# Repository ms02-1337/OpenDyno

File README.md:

# OpenDyno - Open Dynamometer System

> Professional open-source motor dynamometer testing platform.

📖 **Read the full development story:** [Building a Dynamometer From Scratch](https://blog.ms02.es/posts/building-a-dynamometer-from-scratch/)

---

## Overview

**OpenDyno** is a complete open-source dynamometer software and hardware system designed for precise motor/engine performance testing. It is built primarily to control eddy current brakes (it should also support inertia brakes, though this is currently untested).

---

## Architecture

The project is divided into three core parts:

| Component     | Description |
|---------------|-------------|
| **DynoPower** | A power stage PCB designed to control the energy delivered to the eddy current brake. |
| **DynoLogic** | A control PCB running custom firmware. It is responsible for controlling the entire system, executing the logic software, running the PID loops, and managing all safety controls. |
| **DynoServer**| A Flask-based server that can run on a Raspberry Pi or any standard computer. It connects to DynoLogic via CAN bus and acts as the system's user interface. Using WebSockets, it serves a webpage to the browser, allowing the user to configure settings, start/stop tests, store and analyze data, and monitor the brake in real time. |

### Auxiliary Hardware
- **IGBT Power**: An auxiliary power supply board that converts AC mains to 15V to power the IGBT gate driver on the DynoPower board.
  - *Note*: This board is designed to output both +15V and -5V, but **only the positive (+15V) components need to be populated** for the OpenDyno system.

## System

### DynoLogic

### DynoPower

### DynoServer

---

## Key Features

- **Four Control Modes**: Constant Torque, Constant Speed, Dynamic Testing (automated state machine), and Acceleration Rate Control.
- **Real-Time Telemetry**: 100 Hz live data streaming (speed, torque, power, acceleration) via WebSocket.
- **PID Control**: High-frequency closed-loop PID control running at 1 kHz for maximum responsiveness.
- **Data Filtering**: Built-in signal processing including filters to ensure smooth and accurate sensor readings (e.g., from the load cell).
- **Thermal Monitoring**: Support for multiple temperature sensors to monitor brake and ambient temperatures.
- **Safety Limits**: User-configurable maximum speed and maximum PWM limits to protect the eddy current brake from thermal runaway, alongside minimum speed protection, a heartbeat watchdog, and emergency stop.
- **Web Interface**: Responsive UI with live charts.
- **Test Comparison**: Built-in capability to overlay and compare two different test runs directly within the user interface.
- **Selectable Power Units**: Toggle between Kilowatts (kW) and Horsepower (HP) for power measurements.

---

## Operating Modes

OpenDyno supports multiple test modes to thoroughly characterize your motor/engine:

### 1. Dynamic Mode
Automates an entire test run (e.g., accelerating from a minimum to a maximum speed and then decelerating). It uses a state machine to guarantee repeatable and standardized power sweeps.

### 2. Acceleration Mode
Maintains a constant acceleration rate (RPM/s) to smoothly sweep through the motor's power band, ensuring consistent and comparable power measurements regardless of the motor's natural acceleration.

### 3. Torque Mode
Applies a fixed braking torque to the motor regardless of the speed. Useful for thermal testing and checking steady-state efficiency under a specific load.

### 4. Speed Mode
Adjusts the braking force dynamically to hold the motor at an exact RPM, regardless of the throttle position. Perfect for mapping fuel or ignition tables across different RPM bands.

---

## Hardware Specifications

### DynoLogic Control Board
- **MCU**: Teensy 4.1 (600 MHz ARM Cortex-M7)
- **Encoder**: Quadrature input, 50 PPR ×4 (200 counts/rev) with DWT cycle-counter timing
- **Load Cell**: 24-bit ADC (HX711 or ADS1220 selectable at compile time)
- **Brake Control**: 16-bit PWM @ 1 kHz on pin 4
- **Sensors**: MLX90614 IR temperature, BME280 (T+RH), DS18B20, Hall current sensor
- **Communication**: CAN 2.0B @ 500 kbps + USB serial debug @ 500000 baud

### DynoPower Power Board
- **Power Stage**: IGBT-based eddy current brake power stage with isolated gate drive. Rated for up to 1200V and 160A.
- **Rectification**: GBJ5010 bridge rectifier + bulk capacitance
- **Protection**: Thermal monitoring
- **Connectors**: High-current power terminals + 4-pin control interface

### Pinouts & Connectors
See detailed pin assignments in `DynoLogic/README.md` and KiCad schematics.

---

## Getting Started

Building and configuring the OpenDyno system is a multi-step process that involves:

1. Manufacturing and assembling the PCBs (DynoPower, DynoLogic, IGBT Power).
2. Sourcing the components and sensors.
3. Wiring the system.
4. Flashing the DynoLogic firmware.
5. Deploying and configuring the DynoServer software.

To make this process as smooth as possible, we have compiled a comprehensive, chronological step-by-step guide.

> [!IMPORTANT]
> **Please follow the full setup guide here:** [GETTING_STARTED.md](GETTING_STARTED.md)

For detailed configuration parameters and deep-dive technical references, consult the respective component documentation:
- **DynoLogic Reference**: [DynoLogic/README.md](DynoLogic/README.md)
- **DynoPower Reference**: [DynoPower/README.md](DynoPower/README.md)
- **DynoServer Reference**: [DynoServer/README.md](DynoServer/README.md)

---

## Documentation

| Document | Location | Description |
|----------|----------|-------------|
| DynoLogic Reference | `DynoLogic/README.md` | Hardware assembly, firmware compilation, CAN protocol, and configuration parameters |
| DynoPower Reference | `DynoPower/README.md` | Complete guide for the IGBT power stage and brake driver |
| DynoServer Reference| `DynoServer/README.md` | Complete guide for headless Raspberry Pi deployment with systemd |

---

## Safety Warning

⚠️ **This system controls high-power rotating machinery and eddy current brakes.**

- Always use an emergency stop within immediate reach
- Verify all mechanical couplings before applying power
- Never exceed the mechanical or thermal limits of your brake or motor
- Test PID gains at low power first
- Follow all local electrical and mechanical safety regulations

---

## ⚠️ Critical Power-On Sequence

**DynoPower MUST be connected to AC mains ONLY AFTER DynoLogic has fully started and the web UI shows "Connected".**

Failure to follow this sequence can result in:
- Uncontrolled brake actuation on power-up
- Damage to power electronics or eddy current brake

**Correct startup order:**
1. Power on DynoLogic (Teensy boots, firmware initializes)
2. Start DynoServer and verify CAN connection (green "Connected" indicator)
3. **Then** apply AC mains power to DynoPower

**Shutdown order (reverse):**
1. Stop any running test via web UI
2. Remove AC mains power from DynoPower first
3. Power off DynoLogic / DynoServer

---

## Notes to Users

- The system has only been tested with a few amps of power, even though the IGBT supports up to 160A.
- The MAX22530AWE has not been tested in the system. The schematic measures voltage, but isolation has not been tested, and the code for it is not written yet.

---

## License

This project is released under the **Creative Commons Attribution-NonCommercial-ShareAlike 4.0 International (CC BY-NC-SA 4.0)** license:

- ✅ Free to use for personal, educational, and research purposes
- ✅ Must provide attribution to the original authors
- ❌ **Not permitted for commercial use** or any activity that generates revenue
- 🔄 Any modifications or derivative works **must be published** under the exact same license

See the full [LICENSE](LICENSE) file for legal text.

---

*Use at your own risk.*

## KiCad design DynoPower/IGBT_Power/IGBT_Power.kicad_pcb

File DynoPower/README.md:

# DynoPower

> Isolated power electronics board for eddy current brake control.

Part of the **OpenDyno** motor dynamometer system.

## Contents

- `DynoPower_v2/` – KiCad 7 project for the main brake driver
  - `lib/` – Custom component libraries and 3D STEP models
  - `bom/ibom.html` – Interactive bill of materials
- `IGBT_Power/` – KiCad 7 project for the IGBT Driver Power Supply

## Key Features

- IGBT-based brake driver with isolated gate drive (UCC5304)
- GBJ5010 bridge rectifier + bulk capacitance
- Snubber networks and protection circuitry
- High-current power terminals

## Important Safety & Operation Notes

> [!CAUTION]
> **HIGH VOLTAGE**: This board handles dangerous high voltages. Exercise extreme caution and do not touch the board or its terminals while it is powered on. Always allow time for the bulk capacitance to discharge after powering off before handling the board.

> [!WARNING]
> **POWER-ON SEQUENCE**: You must ALWAYS follow the correct power sequencing to avoid unexpected brake engagement or hardware damage:
> 1. Power on the **DynoLogic** controller first.
> 2. Ensure the DynoServer web interface shows a successful **Connected** status.
> 3. **ONLY THEN** should you connect the DynoPower board to AC mains.
> 4. When shutting down, disconnect DynoPower from AC mains *before* powering off DynoLogic.

> [!IMPORTANT]
> **THERMAL MANAGEMENT**: The IGBT on this board is rated for up to 160A. However, a typical eddy current brake will draw between 15A to 45A. If you are operating the brake under constant load for extended periods, the board **will require active cooling (fans)** and a substantial heatsink to dissipate the generated heat.

## Documentation

See the main [OpenDyno README](../README.md#hardware-specifications) for specifications and the KiCad project for schematics and fabrication files.

## License

Licensed under the OpenDyno custom non-commercial license. See root [LICENSE](../LICENSE).

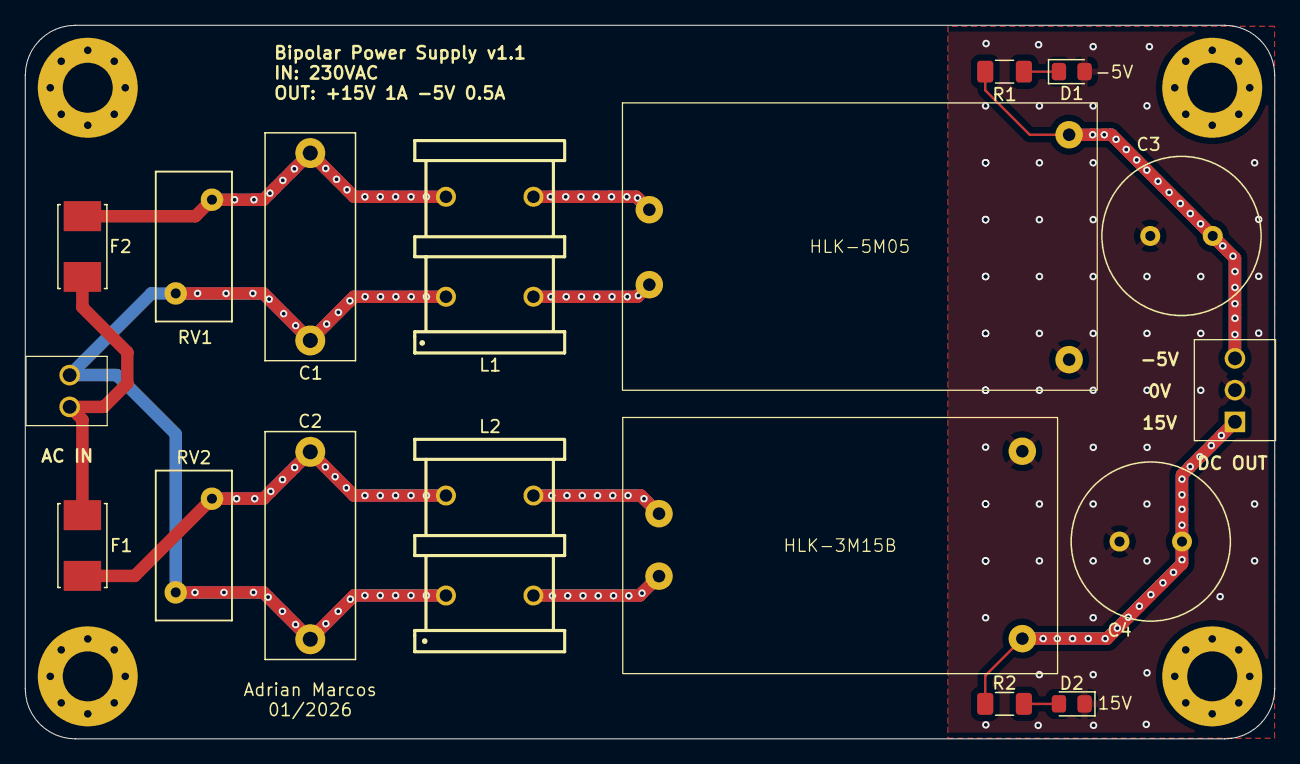
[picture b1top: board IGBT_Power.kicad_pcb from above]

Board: 2 copper layers, 100.0 x 57.1 mm, 22 parts (0 on the bottom side), 13 nets.

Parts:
C1, C2: 0.1uF; C_Rect_L18.0mm_W7.0mm_P15.00mm_FKS3_FKP3
C3, C4: 220uF; C_Radial_D12.5mm_H20.0mm_P5.00mm
D1: 5V; D_0805_2012Metric_Pad1.15x1.40mm_HandSolder
D2: 15V; D_0805_2012Metric_Pad1.15x1.40mm_HandSolder
F1: 1A; Fuseholder_Littelfuse_Nano2_157x
F2: 500mA; Fuseholder_Littelfuse_Nano2_157x
HLK-3M15B: HLK-3M15B
HLK-5M05: HLK-5M05
J1: IN; 2pin
J2: OUT; 3pin
L1, L2: 15mH; 15mH_Inductor
M2, M2#2, M2#3, M2#4: MountingHole_4mm_Pad_Via
R1: 220; R_1206_3216Metric_Pad1.30x1.75mm_HandSolder
R2: 1k; R_1206_3216Metric_Pad1.30x1.75mm_HandSolder
RV1, RV2: 10D561K; RV_Disc_D12mm_W6.1mm_P7.5mm

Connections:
+15V: C4.1, HLK-3M15B.4 (V+), J2.1, R2.1
-5V: C3.2, HLK-5M05.3 (V-), J2.3, R1.2
GND: C3.1, C4.2, D1.2 (A), D2.1 (K), HLK-3M15B.3 (V-), HLK-5M05.4 (V+), J2.2
unnamed: C1.1, F2.1, L1.1, RV1.1
unnamed: C2.1, F1.1, L2.1, RV2.1
unnamed: D1.1 (K), R1.1
unnamed: D2.2 (A), R2.2
unnamed: F1.2, F2.2, J1.1
unnamed: C1.2, C2.2, J1.2, L1.4, L2.4, RV1.2, RV2.2
unnamed: HLK-5M05.1 (AC), L1.2
unnamed: HLK-5M05.2 (AC), L1.3
unnamed: HLK-3M15B.1 (AC), L2.2
unnamed: HLK-3M15B.2 (AC), L2.3

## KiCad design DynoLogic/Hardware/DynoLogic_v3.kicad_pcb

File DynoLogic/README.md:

# DynoLogic

> Real-time embedded dynamometer controller (Teensy 4.1) with multi-mode PID control and CAN bus communication.

Part of the **OpenDyno** motor dynamometer system.

## 1. Firmware Configuration (`config.h`)

For a complete step-by-step assembly and setup guide, please see [../GETTING_STARTED.md](../GETTING_STARTED.md). 

The firmware provides several compile-time parameters that must be set to match your exact hardware setup. These are found in **`Firmware/include/config.h`**.

### Load Cell Type (CRITICAL)
The DynoLogic board supports two different ADCs for the load cell. You **must** define exactly one of them in `config.h` by uncommenting the appropriate line:
```cpp
// LOAD CELL SELECTION
//#define USE_HX711_LOAD_CELL                 // External HX711 amplifier (legacy)
#define USE_ADS1220_LOAD_CELL                 // Internal ADS1220 24-bit ADC (default for DynoLogic v3)
```

### Encoder Resolution
Set the number of pulses per revolution (PPR) of your rotary encoder. The firmware uses hardware quadrature decoding, so the actual counts per revolution will be 4× this value.
```cpp
#define ENC_PPR 50                            // Base resolution of your encoder
#define ENC_REVERSE_DIRECTION 1               // Reverse quadrature sign to ensure positive RPM
```

### Brake Safety Limits
Set hard limits for the PWM duty cycle and operating speeds to prevent thermal runaway or mechanical failure.
```cpp
#define DEFAULT_MAXIMUM_SPEED 4500            // Maximum operating speed [RPM]
#define DEFAULT_MAX_PWM_OUTPUT 330            // Maximum PWM value
```

### Signal Filtering
The system uses cascaded low-pass filters to clean up noisy sensor data. You can tune the aggressiveness of these filters:
```cpp
#define LOW_PASS_FILTER_SPEED_FREQ 20.0       // Speed filter cutoff [Hz]
#define LOW_PASS_FILTER_TORQUE_FREQ 15.0      // Torque filter cutoff [Hz]
```

> [!TIP]
> While these are the default firmware values, parameters like PID gains, minimum/maximum RPM, and filter cutoffs can also be tuned live via the DynoServer web interface!

## 2. Building and Flashing

### Prerequisites
1. Install [PlatformIO](https://platformio.org/install)
2. Clone this repository
3. Connect the Teensy 4.1 via USB

### Build Commands

```bash
# Build the project
pio run

# Upload to Teensy 4.1
pio run --target upload

# Clean build artifacts
pio run --target clean

# Monitor serial output (500000 baud)
pio device monitor

# Upload and monitor in one command
pio run --target upload && pio device monitor
```

## 3. Features & Specifications

- **Multiple Control Modes**
  - Torque control mode with load cell feedback
  - Speed control mode with rotary encoder feedback
  - Acceleration control mode
  - Dynamic testing mode with automated state machine

- **High-Performance Sensors**
  - Rotary encoder with DWT cycle-counter timing for precise speed measurement
  - 24-bit load cell ADC (HX711 or ADS1220 @ 2 kSPS turbo) for torque measurement
  - MLX90614 IR temperature sensor for brake monitoring
  - Hall effect current sensor
  - Environmental sensors (BME280, DS18B20)

- **Real-Time Control**
  - 1ms PID control loop (1000Hz update rate)
  - Multi-rate task scheduling (1ms, 10ms, 100ms, 500ms, 1s, 5s)
  - Configurable cascaded low-pass filtering

- **Safety Features**
  - Configurable speed limits (min/max)
  - PWM output limits
  - Configuration checksum validation
  - Heartbeat monitoring

## 4. Hardware Setup

The DynoLogic control board (`DynoLogic_v3`) is the brains of the operation. It interfaces with the sensors and controls the eddy current brake via the DynoPower board.

- **Schematics & PCB**: The full KiCad 7 project is located in `Hardware/`.
- **Manufacturing**: To manufacture the PCB, use the pre-generated Gerbers found at `Hardware/Gerbers/DynoLogic_v3.zip`.
- **Assembly**: Use the interactive bill of materials at `Hardware/bom/ibom.html` to easily place and solder components.

### Pin Assignments
```
┌─────────────────────────────────────────────────────────────────┐
│                    Teensy 4.1 Pin Assignments                   │
├─────────────────────────────────────────────────────────────────┤
│  PWM Output (Brake)                                             │
│  ├── Pin 4: PWM output (16-bit, 1kHz)                           │
│                                                                 │
│  Encoder (Quadrature)                                           │
│  ├── Pin 2: Phase A (interrupt, rising edge)                    │
│  ├── Pin 3: Phase B (interrupt, rising edge)                    │
│                                                                 │
│  Load Cell (HX711 - Alternative)                                │
│  ├── Pin 8: CLK (clock)                                         │
│  ├── Pin 9: DAT (data)                                          │
│                                                                 │
│  Load Cell (ADS1220 - Default, shares SPI0 with MAX22530)       │
│  ├── Pin 10: CS (chip select)                                   │
│  ├── Pin 41: DRDY (data ready, ISR-driven)                      │
│  └── SPI0: MOSI=11, MISO=12, SCK=13                             │
│                                                                 │
│  Temperature Sensors                                            │
│  ├── Pins 16/17: BME280 on Wire1 (SCL1/SDA1, addr 0x76)         │
│  ├── Pin 15: OneWire bus (DS18B20)                              │
│  └── Wire (I2C0): MLX90614 IR temperature sensor                │
│                                                                 │
│  Current/Voltage Measurement                                    │
│  ├── Pin A10: Hall effect current sensor (12-bit ADC)           │
│  ├── Pin 0:  MAX22530 CS (hardware feature, unused in firmware) │
└─────────────────────────────────────────────────────────────────┘
```

## 5. System Architecture

### CAN Bus Protocol
- **Microcontroller → Server**: `0x01 - 0x13`
- **Server → Microcontroller**: `0x100 - 0x126`

### Multi-Rate Control Loop
```
┌──────────────────────────────────────────────────────────────┐
│  1ms Timer ISR                                               │
│  └── Sets timing flags for multi-rate scheduling            │
├──────────────────────────────────────────────────────────────┤
│  Main Loop                                                   │
│  ├── 1ms:  PID control (1000Hz)                             │
│  ├── 10ms: Real-time data transmission                      │
│  ├── 100ms: CAN TX/RX, electrical data                      │
│  ├── 500ms: System status, LED heartbeat                    │
│  ├── 1s: Temperature readings, config reset                 │
│  └── 5s: Maintenance tasks                                  │
└──────────────────────────────────────────────────────────────┘
```

### Signal Processing Chain
```
Raw Sensor Data
    │
    ▼
Cascaded Low-Pass Filter (configurable cutoff)
    │
    ▼
Control System / CAN Transmission
```

## 6. Directory Structure

- `Firmware/` – PlatformIO C++ firmware (`src/`, `include/`, `platformio.ini`)
- `Hardware/` – KiCad 7 project (`DynoLogic_v3`), libraries, BOM, backups

## 7. Safety Considerations

> [!CAUTION]
> This system controls high-power eddy current brakes. Ensure:
> - Proper mechanical mounting and coupling
> - Emergency stop functionality is tested
> - Load cell is properly calibrated before use
> - Speed limits are configured appropriately for your equipment
> - PWM limits are set conservatively on first use
> - System is monitored during operation

## License

Licensed under the OpenDyno custom non-commercial license. See root [LICENSE](../LICENSE).

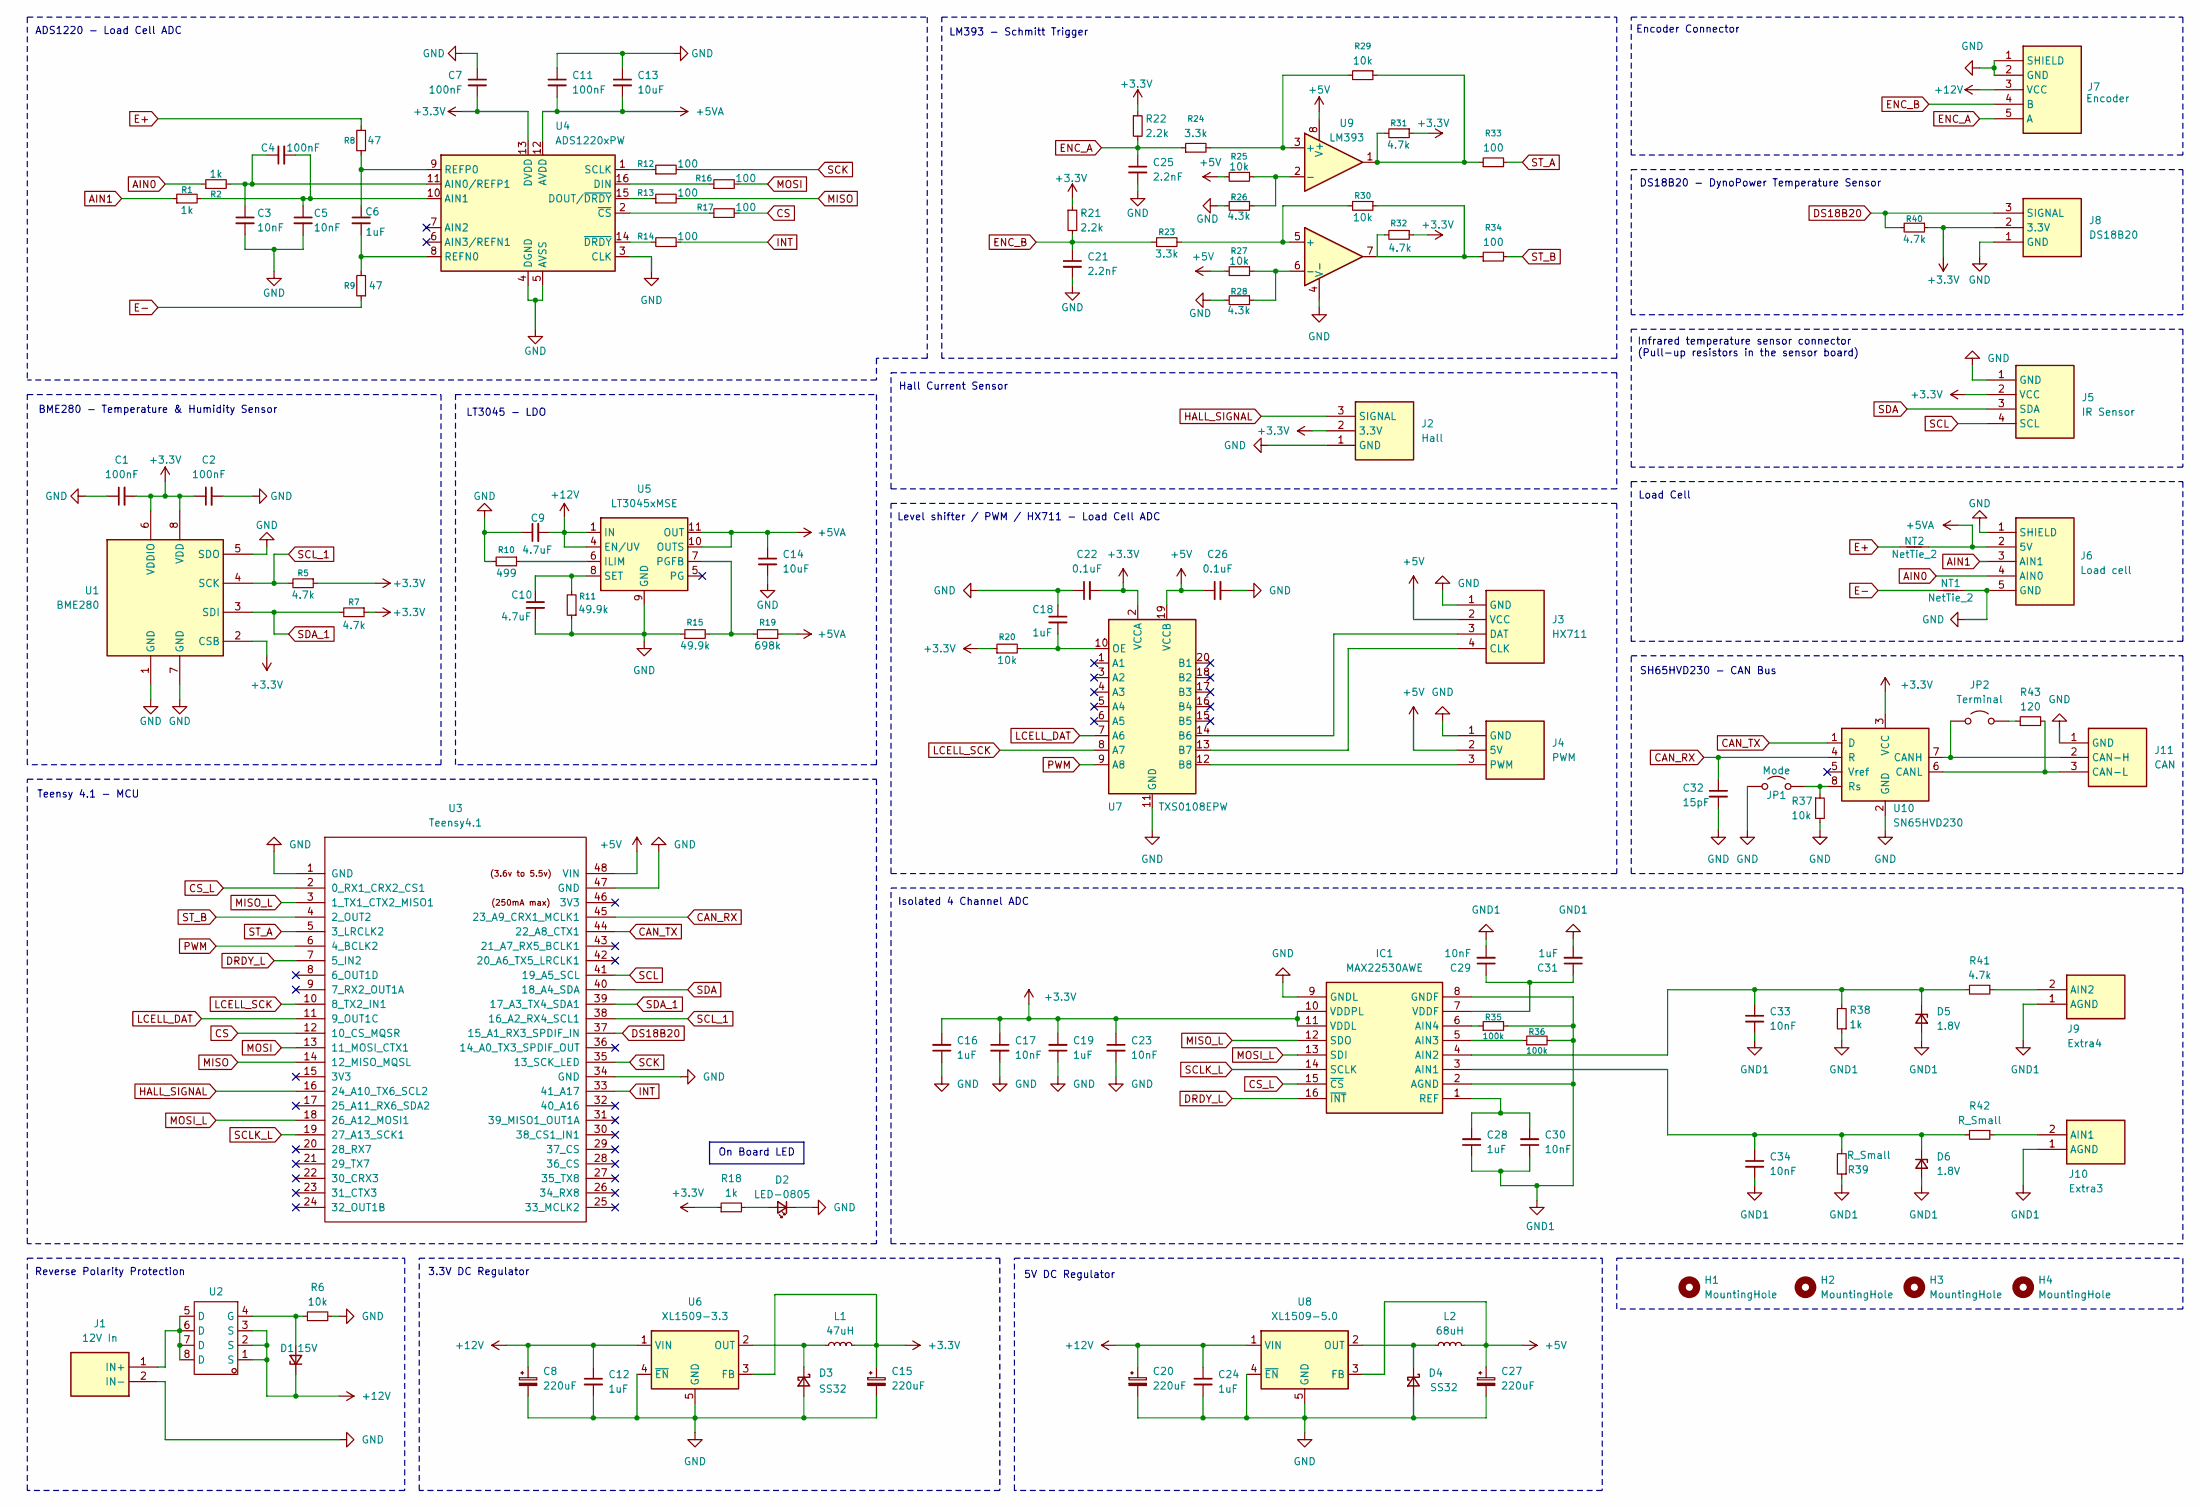
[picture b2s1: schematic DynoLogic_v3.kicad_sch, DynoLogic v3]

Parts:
C1, C2, C4, C7, C11: 100nF; C_1206_3216Metric
C3, C5, C17, C23, C29, C30, C33, C34: 10nF; C_1206_3216Metric
C6, C12, C16, C18, C19, C24, C28, C31: 1uF; C_1206_3216Metric
C8, C15, C20, C27: 220uF; CP_Elec_6.3x7.7
C9, C10: 4.7uF; C_1206_3216Metric
C13, C14: 10uF; C_1206_3216Metric
C21, C25: 2.2nF; C_1206_3216Metric
C22, C26: 0.1uF; C_1206_3216Metric
C32: 15pF; C_1206_3216Metric
D1: 15V; SOT-23_Handsoldering
D2: LED-0805; LED_0805_2012Metric_Pad1.15x1.40mm_HandSolder
D3, D4: SS32; D_SMA
D5, D6: 1.8V; D_SOD-123
H1, H2, H3, H4: MountingHole; MountingHole_4mm_Pad_Via
IC1: MAX22530AWE; Mouser Part Number 700-MAX22530AWET
J1: 12V In; Connector_2pin; Mouser Part Number 538-39773-0002
J2: Hall; Connector_3pin; Mouser Part Number 538-39773-0003
J3: HX711; Connector_4pin; Mouser Part Number 538-39773-0004
J4: PWM; Connector_3pin; Mouser Part Number 538-39773-0003
J5: IR Sensor; Connector_4pin; Mouser Part Number 538-39773-0004
J6: Load cell; Connector_5pin; Mouser Part Number 651-1725685
J7: Encoder; Connector_5pin; Mouser Part Number 651-1725685
J8: DS18B20; Connector_3pin; Mouser Part Number 538-39773-0003
J9: Extra4; Connector_2pin; Mouser Part Number 538-39773-0002
J10: Extra3; Connector_2pin; Mouser Part Number 538-39773-0002
J11: CAN; Connector_3pin; Mouser Part Number 538-39773-0003
JP1: Mode; SolderJumper-2_P1.3mm_Open_Pad1.0x1.5mm
JP2: Terminal; SolderJumper-2_P1.3mm_Open_Pad1.0x1.5mm
L1: 47uH; Regulator_L
L2: 68uH; Regulator_L
NT1, NT2: NetTie_2; NetTie-2_SMD_Pad0.5mm
R1, R2, R18, R38: 1k; R_1206_3216Metric
R5, R7, R31, R32, R40, R41: 4.7k; R_1206_3216Metric
R6, R20, R25, R27, R29, R30, R37: 10k; R_1206_3216Metric
R8, R9: 47; R_1206_3216Metric
R10: 499; R_1206_3216Metric
R11, R15: 49.9k; R_1206_3216Metric
R12, R13, R14, R16, R17, R33, R34: 100; R_1206_3216Metric
R19: 698k; R_1206_3216Metric
R21, R22: 2.2k; R_1206_3216Metric
R23, R24: 3.3k; R_1206_3216Metric
R26, R28: 4.3k; R_1206_3216Metric
R35, R36: 100k; R_1206_3216Metric
R39, R42: R_Small; R_1206_3216Metric
R43: 120; R_1206_3216Metric
U1: BME280
U2: FDS6675BZ1; FDS6675; Manufacturer Part FDS6675BZ; LCSC Part Name 1个P沟道 耐压:30V 电流:11A
U3: Teensy4.1; Teensy41
U4: ADS1220xPW; TSSOP-16_4.4x5mm_P0.65mm
U5: LT3045xMSE; MSOP-12-1EP_3x4.039mm_P0.65mm_EP1.651x2.845mm
U6: XL1509-3.3; SOIC-8_3.9x4.9mm_P1.27mm
U7: TXS0108EPW; TSSOP-20_4.4x6.5mm_P0.65mm
U8: XL1509-5.0; SOIC-8_3.9x4.9mm_P1.27mm
U9: LM393; SOIC-8_3.9x4.9mm_P1.27mm
U10: SN65HVD230; SOIC-8_3.9x4.9mm_P1.27mm

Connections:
+3.3V: C1.2, C2.1, C7.2, C15.1, C16.2, C17.1, C19.2, C22.2, C23.1, IC1.10 (VDDPL), IC1.11 (VDDL), J2.2 (3.3V), J5.2 (VCC), J8.2 (3.3V), L1.2, R5.1, R7.1, R18.1, R20.1, R21.1, R22.1, R31.1, R32.1, R40.1, U1.2 (CSB), U1.6 (VDDIO), U1.8 (VDD), U4.13 (DVDD), U6.3 (FB), U7.2 (VCCA), U10.3 (VCC)
+5V: C26.1, C27.1, J3.2 (VCC), J4.2 (5V), L2.2, R25.2, R27.2, U3.48 (VIN), U7.19 (VCCB), U8.3 (FB), U9.8 (V+)
+5VA: C11.2, C13.2, C14.1, J6.2 (5V), NT2.2, R19.2, U4.12 (AVDD), U5.10 (OUTS), U5.11 (OUT), U5.12 (OUT)
+12V: C8.1, C9.2, C12.1, C20.1, C24.1, D1.1 (K), J7.3 (VCC), U2.1 (S), U2.2 (S), U2.3 (S), U5.1 (IN), U5.2 (IN), U5.3 (IN), U5.4 (EN/UV), U6.1 (VIN), U8.1 (VIN)
AIN0: J6.4 (AIN0), R2.1
AIN1: J6.3 (AIN1), R1.1
CAN_RX: C32.1, U3.45 (23_A9_CRX1_MCLK1), U10.4 (R)
CAN_TX: U3.44 (22_A8_CTX1), U10.1 (D)
CS: R17.2, U3.12 (10_CS_MQSR)
CS_L: IC1.15 (~CS), U3.2 (0_RX1_CRX2_CS1)
DRDY_L: IC1.16 (~INT), U3.7 (5_IN2)
DS18B20: J8.3 (SIGNAL), R40.2, U3.37 (15_A1_RX3_SPDIF_IN)
E+: NT2.1, R8.2
E-: NT1.1, R9.1
ENC_A: C25.1, J7.5 (A), R22.2, R24.1
ENC_B: C21.1, J7.4 (B), R21.2, R23.1
GND: C1.1, C2.2, C3.2, C5.2, C7.1, C8.2, C9.1, C10.2, C11.1, C12.2, C13.1, C14.2, C15.2, C16.1, C17.2, C18.1, C19.1, C20.2, C21.2, C22.1, C23.2, C24.2, C25.2, C26.2, C27.2, C32.2, D2.1 (K), D3.2 (A), D4.2 (A), IC1.9 (GNDL), J1.2 (IN-), J2.1 (GND), J3.1 (GND), J4.1 (GND), J5.1 (GND), J6.1 (SHIELD), J6.5 (GND), J7.1 (SHIELD), J7.2 (GND), J8.1 (GND), J11.1 (GND), JP1.1 (A), NT1.2, R6.2, R10.2, R11.1, R15.1, R26.2, R28.2, R37.2, U1.1 (GND), U1.5 (SDO), U1.7 (GND), U3.1 (GND), U3.34 (GND), U3.47 (GND), U4.3 (CLK), U4.4 (DGND), U4.5 (AVSS), U5.9 (GND), U5.13 (GND), U6.4 (~EN), U6.5 (GND), U6.6 (GND), U6.7 (GND), U6.8 (GND), U7.11 (GND), U8.4 (~EN), U8.5 (GND), U8.6 (GND), U8.7 (GND), U8.8 (GND), U9.4 (V-), U10.2 (GND)
GND1: C28.1, C29.2, C30.1, C31.2, C33.2, C34.2, D5.2 (A), D6.2 (A), IC1.2 (AGND), IC1.8 (GNDF), J9.1 (AGND), J10.1 (AGND), R35.2, R36.2, R38.1, R39.1
HALL_SIGNAL: J2.3 (SIGNAL), U3.16 (24_A10_TX6_SCL2)
INT: R14.1, U3.33 (41_A17)
LCELL_DAT: U3.11 (9_OUT1C), U7.7 (A6)
LCELL_SCK: U3.10 (8_TX2_IN1), U7.8 (A7)
MISO: R13.2, U3.14 (12_MISO_MQSL)
MISO_L: IC1.12 (SDO), U3.3 (1_TX1_CTX2_MISO1)
MOSI: R16.2, U3.13 (11_MOSI_CTX1)
MOSI_L: IC1.13 (SDI), U3.18 (26_A12_MOSI1)
unnamed: D1.2 (A), R6.1, U2.4 (G)
unnamed: D2.2 (A), R18.2
unnamed: D3.1 (K), L1.1, U6.2 (OUT)
unnamed: D4.1 (K), L2.1, U8.2 (OUT)
unnamed: C33.1, D5.1 (K), IC1.4 (AIN2), R38.2, R41.2
unnamed: C34.1, D6.1 (K), IC1.3 (AIN1), R39.2, R42.2
unnamed: IC1.5 (AIN3), R36.1
unnamed: IC1.6 (AIN4), R35.1
unnamed: C28.2, C30.2, IC1.1 (REF)
unnamed: C29.1, C31.1, IC1.7 (VDDF)
unnamed: J1.1 (IN+), U2.5 (D), U2.6 (D), U2.7 (D), U2.8 (D)
unnamed: J3.4 (CLK), U7.13 (B7)
unnamed: J3.3 (DAT), U7.14 (B6)
unnamed: J4.3 (PWM), U7.12 (B8)
unnamed: J9.2 (AIN2), R41.1
unnamed: J10.2 (AIN1), R42.1
unnamed: J11.2 (CAN-H), JP2.1 (A), U10.7 (CANH)
unnamed: J11.3 (CAN-L), R43.2, U10.6 (CANL)
unnamed: JP1.2 (B), R37.1, U10.8 (Rs)
unnamed: JP2.2 (B), R43.1
unnamed: R23.2, R30.2, U9.5 (+)
unnamed: R24.2, R29.2, U9.3 (+)
unnamed: R25.1, R26.1, U9.2 (-)
unnamed: R27.1, R28.1, U9.6 (-)
unnamed: R29.1, R31.2, R33.1, U9.1
unnamed: R30.1, R32.2, R34.1, U9.7
unnamed: C3.1, C4.1, R2.2, U4.11 (AIN0/REFP1)
unnamed: C4.2, C5.1, R1.2, U4.10 (AIN1)
unnamed: R16.1, U4.16 (DIN)
unnamed: R13.1, U4.15 (DOUT/~DRDY)
unnamed: C6.2, R9.2, U4.8 (REFN0)
unnamed: C6.1, R8.1, U4.9 (REFP0)
unnamed: R12.1, U4.1 (SCLK)
unnamed: R17.1, U4.2 (~CS)
unnamed: R14.2, U4.14 (~DRDY)
unnamed: R10.1, U5.6 (ILIM)
unnamed: R15.2, R19.1, U5.7 (PGFB)
unnamed: C10.1, R11.2, U5.8 (SET)
unnamed: C18.2, R20.2, U7.10 (OE)
PWM: U3.6 (4_BCLK2), U7.9 (A8)
SCK: R12.2, U3.35 (13_SCK_LED)
SCL: J5.4 (SCL), U3.41 (19_A5_SCL)
SCLK_L: IC1.14 (SCLK), U3.19 (27_A13_SCK1)
SCL_1: R5.2, U1.4 (SCK), U3.38 (16_A2_RX4_SCL1)
SDA: J5.3 (SDA), U3.40 (18_A4_SDA)
SDA_1: R7.2, U1.3 (SDI), U3.39 (17_A3_TX4_SDA1)
ST_A: R33.2, U3.5 (3_LRCLK2)
ST_B: R34.2, U3.4 (2_OUT2)

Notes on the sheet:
Hall Current Sensor
ADS1220 - Load Cell ADC
Load Cell
LM393 - Schmitt Trigger
DS18B20 - DynoPower Temperature Sensor
Isolated 4 Channel ADC
SH65HVD230 - CAN Bus
5V DC Regulator
Infrared temperature sensor connector (Pull-up resistors in the sensor board)
Level shifter / PWM / HX711 - Load Cell ADC
3.3V DC Regulator
Encoder Connector
Teensy 4.1 - MCU
Reverse Polarity Protection
BME280 - Temperature & Humidity Sensor
LT3045 - LDO
On Board LED

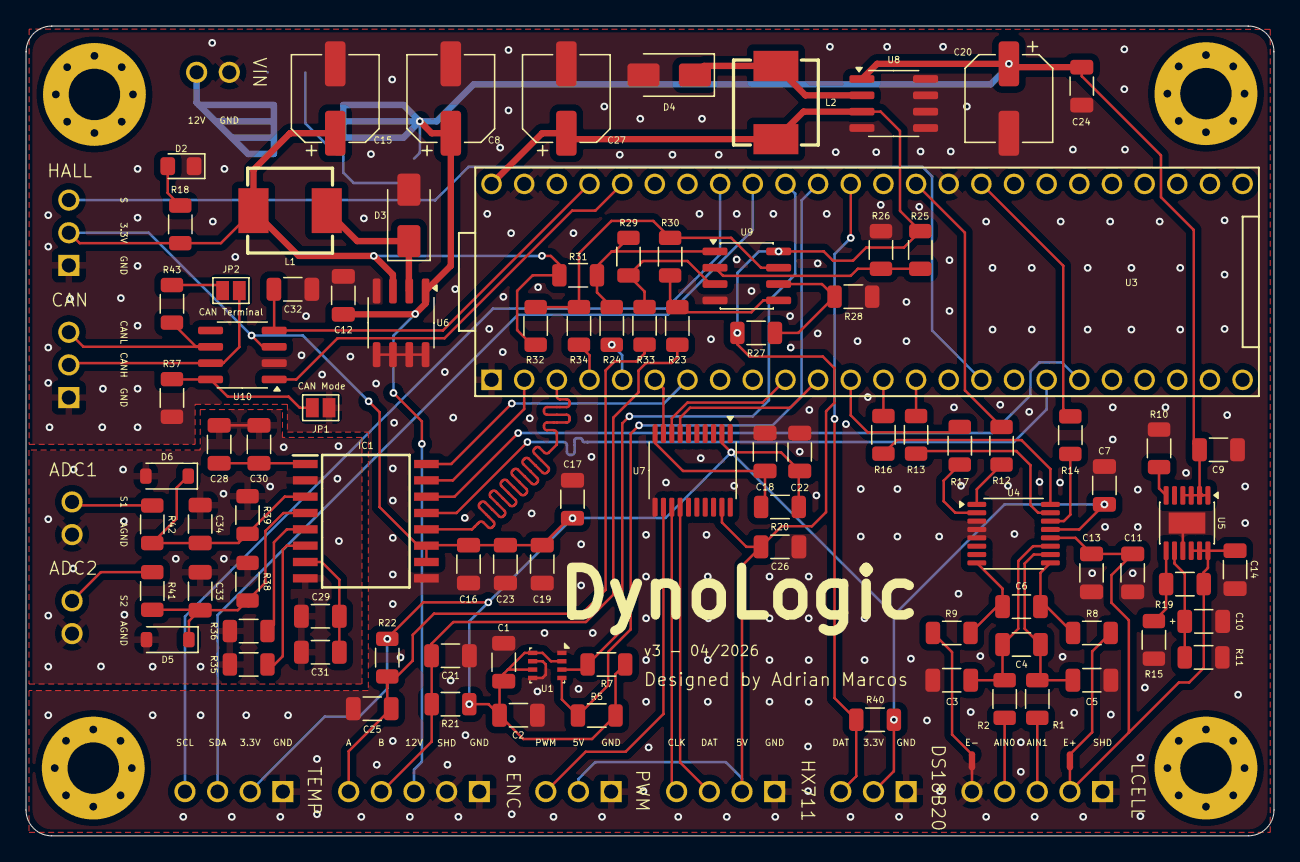
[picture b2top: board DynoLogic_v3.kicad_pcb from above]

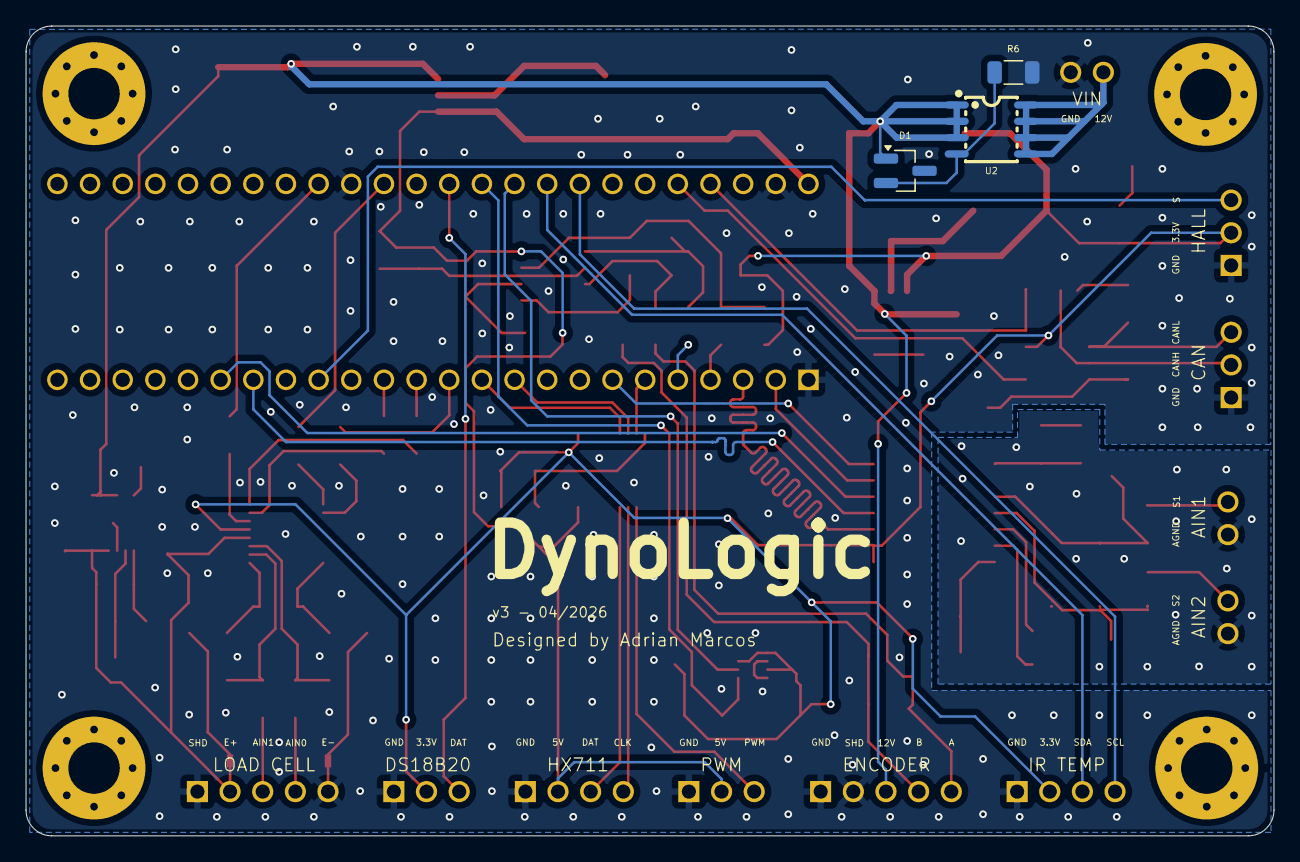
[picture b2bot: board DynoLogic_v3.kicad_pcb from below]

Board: 2 copper layers, 97.1 x 63.0 mm, 113 parts (3 on the bottom side), 74 nets.

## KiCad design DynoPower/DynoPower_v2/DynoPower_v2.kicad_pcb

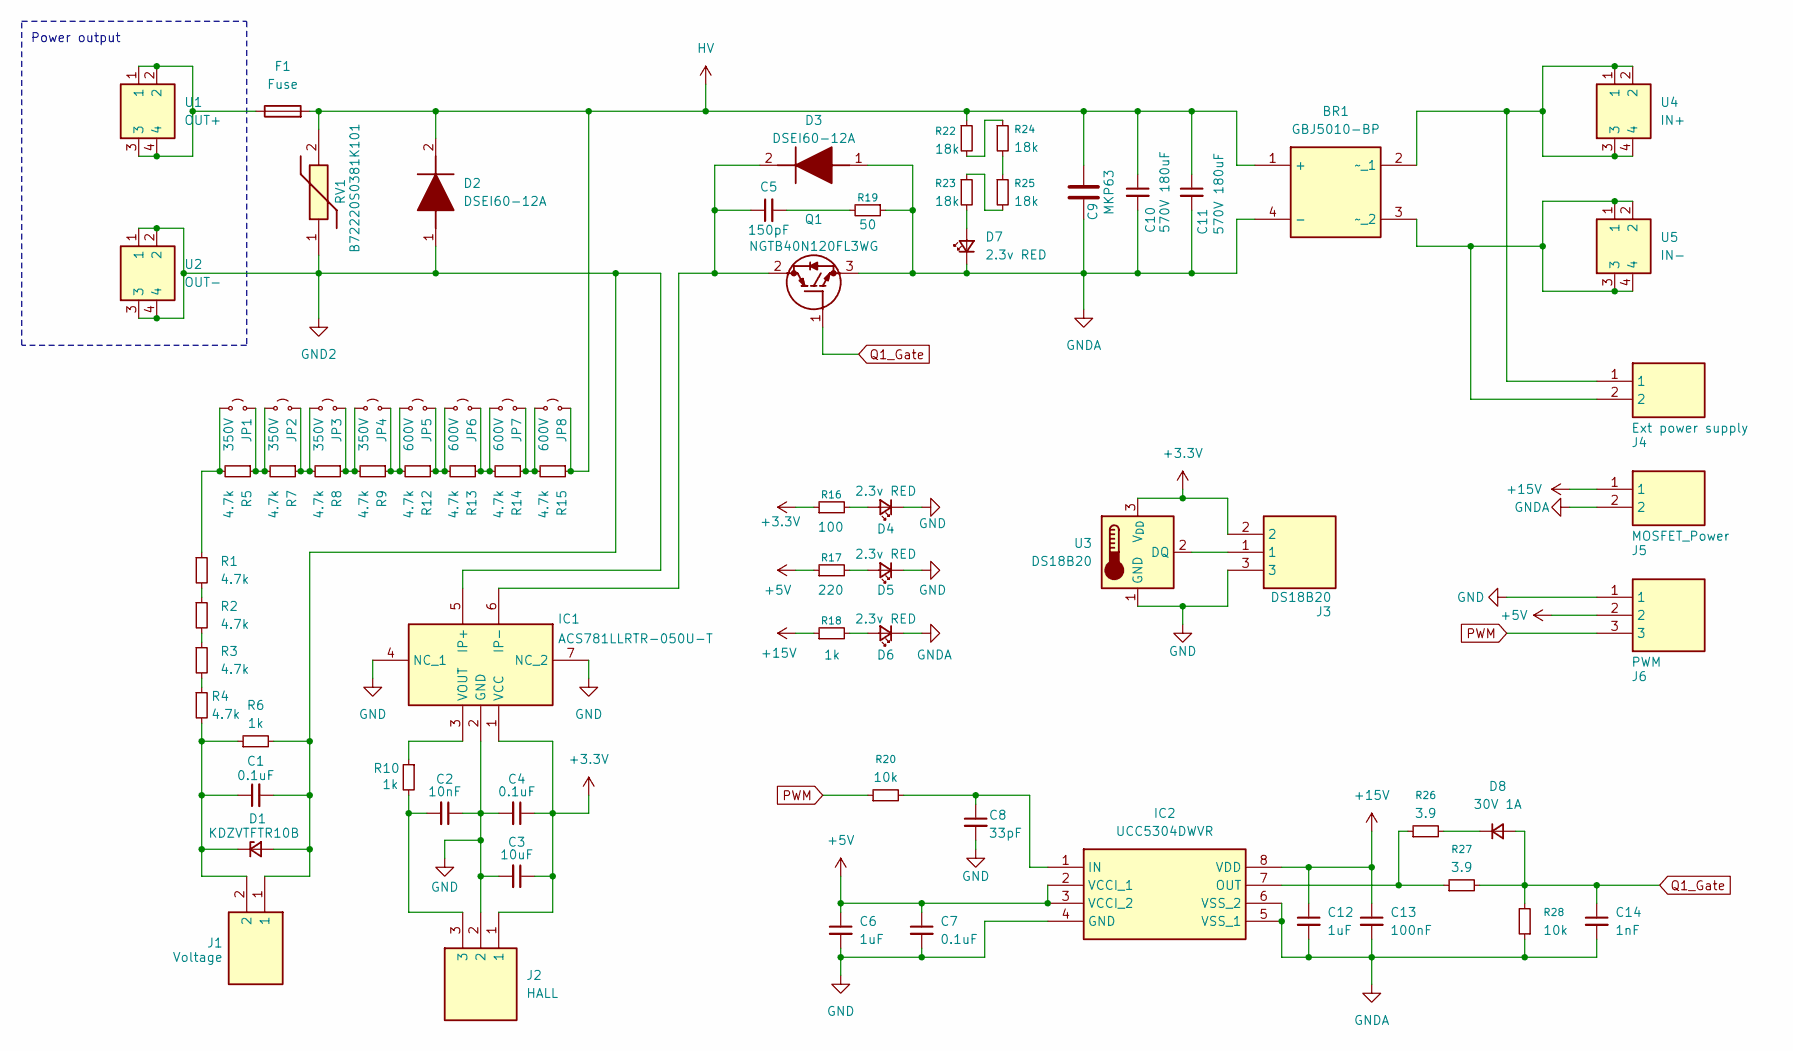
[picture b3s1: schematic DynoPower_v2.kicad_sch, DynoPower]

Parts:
BR1: GBJ5010-BP; GBJ5010; Mouser Part Number 833-GBJ5010-BP
C1, C4: 0.1uF; C_1206_3216Metric
C2: 10nF; C_1206_3216Metric
C3: 10uF; C_1206_3216Metric
C5: 150pF; C_1206_3216Metric_Pad1.33x1.80mm_HandSolder
C6, C12: 1uF; C_1206_3216Metric_Pad1.33x1.80mm_HandSolder
C7: 0.1uF; C_1206_3216Metric_Pad1.33x1.80mm_HandSolder
C8: 33pF; C_1206_3216Metric_Pad1.33x1.80mm_HandSolder
C9: MKP63; KNB2520
C10, C11: 570V 180uF; Capacitor
C13: 100nF; C_1206_3216Metric_Pad1.33x1.80mm_HandSolder
C14: 1nF; C_0603_1608Metric_Pad1.08x0.95mm_HandSolder
D1: KDZVTFTR10B; D_SOD-123F
D2, D3: DSEI60-12A; Mouser Part Number 747-DSEI60-12A
D4, D5, D6, D7: 2.3v RED; D_0805_2012Metric_Pad1.15x1.40mm_HandSolder
D8: 30V 1A; D_SOD-123
F1: Fuse; Fuseholder_Clip-6.3x32mm_Littelfuse_102_122_Inline_P34.21x7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
IC1: ACS781LLRTR-050U-T; ACS780LLRTR050BT; Mouser Part Number 250-781LLRTR100BT
IC2: UCC5304DWVR; Mouser Part Number 595-UCC5304DWVR
J1: Voltage; Connector_2pin; Mouser Part Number 538-39773-0002
J2: HALL; Connector_3pin; Mouser Part Number 538-39773-0003
J3: DS18B20; Connector_3pin; Mouser Part Number 538-39773-0003
J4: Ext power supply; Connector_2pin; Mouser Part Number 538-39773-0002
J5: MOSFET_Power; Connector_2pin; Mouser Part Number 538-39773-0002
J6: PWM; Connector_3pin; Mouser Part Number 538-39773-0003
JP1, JP2, JP3, JP4: 350V; SolderJumper-2_P1.3mm_Open_RoundedPad1.0x1.5mm
JP5, JP6, JP7, JP8: 600V; SolderJumper-2_P1.3mm_Open_RoundedPad1.0x1.5mm
Q1: NGTB40N120FL3WG; Mouser Part Number 863-NGTB40N120FL3WG
R1, R2, R3, R4, R5, R7, R8, R9, R12, R13, R14, R15: 4.7k; R_1206_3216Metric
R6, R10: 1k; R_1206_3216Metric
R16: 100; R_1206_3216Metric
R17: 220; R_1206_3216Metric_Pad1.30x1.75mm_HandSolder
R18: 1k; R_1206_3216Metric_Pad1.30x1.75mm_HandSolder
R19: 50; R_1206_3216Metric_Pad1.30x1.75mm_HandSolder
R20, R28: 10k; R_1206_3216Metric_Pad1.30x1.75mm_HandSolder
R22, R23, R24, R25: 18k; R_2512_6332Metric_Pad1.40x3.35mm_HandSolder
R26, R27: 3.9; R_2512_6332Metric_Pad1.40x3.35mm_HandSolder
RV1: B72220S0381K101; Mouser Part Number 871-B72220S381K101
U1: OUT+; PowerTerminal_S
U2: OUT-; PowerTerminal_S
U3: DS18B20; TO-92_Inline
U4: IN+; PowerTerminal_S
U5: IN-; PowerTerminal_S

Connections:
+3.3V: C3.1, C4.1, IC1.1 (VCC), J2.1, J3.2, R16.1, U3.3 (V_{DD})
+5V: C6.1, C7.1, IC2.2 (VCCI_1), IC2.3 (VCCI_2), J6.2, R17.1
+15V: C12.1, C13.1, IC2.8 (VDD), J5.1, R18.1
GND: C2.1, C3.2, C4.2, C6.2, C7.2, C8.2, D4.1 (K), D5.1 (K), IC1.2 (GND), IC1.4 (NC_1), IC1.7 (NC_2), IC2.4 (GND), J2.2, J3.3, J6.1, U3.1 (GND)
GND2: C1.2, D1.2 (A), D2.1 (A), IC1.5 (IP+), J1.1, R6.2, RV1.1, U2.1, U2.2, U2.3, U2.4
GNDA: BR1.4 (-), C9.2, C10.2, C11.2, C12.2, C13.2, C14.2, D3.1 (A), D6.1 (K), D7.1 (K), IC2.5 (VSS_1), IC2.6 (VSS_2), J5.2, Q1.3 (E), R19.1, R28.1
HV: BR1.1 (+), C9.1, C10.1, C11.1, D2.2 (K), F1.2, JP8.2 (B), R15.1, R22.1, RV1.2
unnamed: BR1.2 (~_1), J4.1, U4.1, U4.2, U4.3, U4.4
unnamed: BR1.3 (~_2), J4.2, U5.1, U5.2, U5.3, U5.4
unnamed: C2.2, J2.3, R10.2
unnamed: C5.2, R19.2
unnamed: C1.1, D1.1 (K), J1.2, R4.2, R6.1
unnamed: C5.1, D3.2 (K), IC1.6 (IP-), Q1.2 (C)
unnamed: D4.2 (A), R16.2
unnamed: D5.2 (A), R17.2
unnamed: D6.2 (A), R18.2
unnamed: D7.2 (A), R23.2
unnamed: D8.1 (K), R26.2
unnamed: F1.1, U1.1, U1.2, U1.3, U1.4
unnamed: IC1.3 (VOUT), R10.1
unnamed: C8.1, IC2.1 (IN), R20.2
unnamed: IC2.7 (OUT), R26.1, R27.1
unnamed: JP1.1 (A), R1.1, R5.2
unnamed: JP1.2 (B), JP2.1 (A), R5.1, R7.2
unnamed: JP2.2 (B), JP3.1 (A), R7.1, R8.2
unnamed: JP3.2 (B), JP4.1 (A), R8.1, R9.2
unnamed: JP4.2 (B), JP5.1 (A), R9.1, R12.2
unnamed: JP5.2 (B), JP6.1 (A), R12.1, R13.2
unnamed: JP6.2 (B), JP7.1 (A), R13.1, R14.2
unnamed: JP7.2 (B), JP8.1 (A), R14.1, R15.2
unnamed: R1.2, R2.1
unnamed: R2.2, R3.1
unnamed: R3.2, R4.1
unnamed: R22.2, R24.1
unnamed: R23.1, R25.2
unnamed: R24.2, R25.1
unnamed: J3.1, U3.2 (DQ)
PWM: J6.3, R20.1
Q1_Gate: C14.1, D8.2 (A), Q1.1 (G), R27.2, R28.2

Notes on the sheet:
Power output

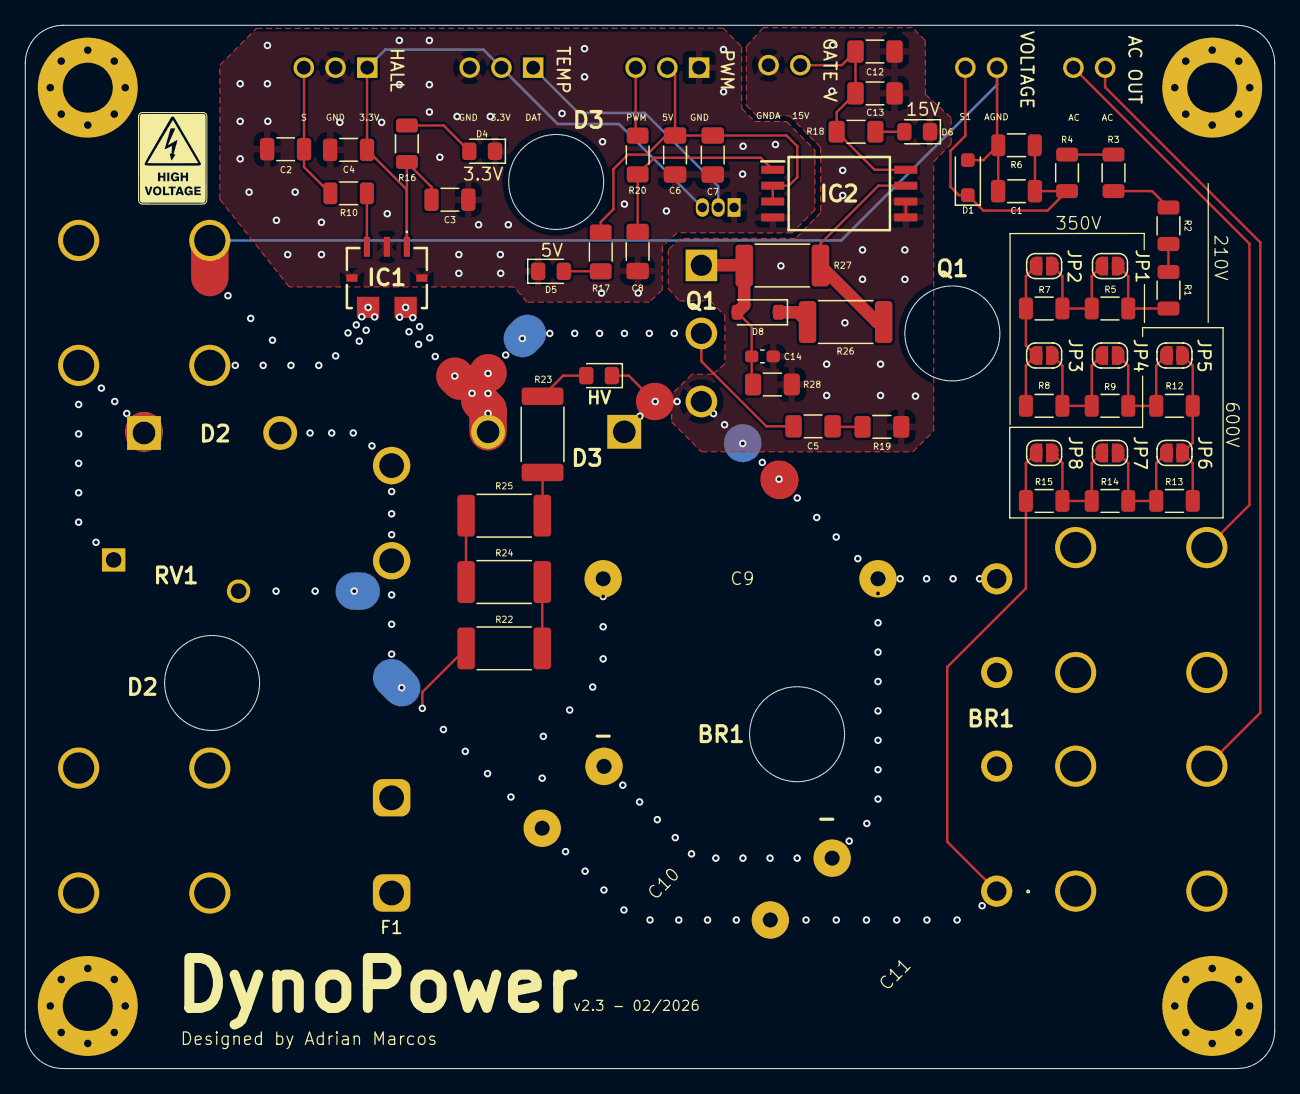
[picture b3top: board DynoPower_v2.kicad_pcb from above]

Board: 2 copper layers, 100.0 x 83.5 mm, 73 parts (1 on the bottom side), 39 nets.

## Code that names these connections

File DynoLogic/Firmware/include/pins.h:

// pins.h - Teensy 4.1 pin assignments for DynoLogic

#ifndef PINS_H
#define PINS_H

// LOAD CELL (HX711 - external 24-bit ADC, optional)
#define HX711_DAT 9   // HX711 data pin (DOUT)
#define HX711_CLK 8   // HX711 clock pin (PD_SCK)

// INTERNAL ADS1220 LOAD CELL ADC
// Shares default SPI bus (SPI0) with the MAX22530 voltage ADC.
// SPI0 pins on Teensy 4.1: MOSI=11, MISO=12, SCK=13.
#define ADS_SPI     SPI    // Default SPI0 instance
#define PIN_DRDY    41     // Data Ready signal (active LOW)
#define PIN_CS      10     // Chip Select for ADS1220

// ACTUATOR CONTROL
#define PWM_PIN 4         // PWM output to eddy current brake (16-bit hardware PWM)

// ENVIRONMENTAL SENSORS
#define BME280_WIRE     Wire1   // I2C1 bus (SCL1=16, SDA1=17)
#define BME280_I2C_ADDR 0x76    // I2C address (SDO tied to GND)
#define ONE_WIRE_BUS    15      // DS18B20 temperature sensor (OneWire bus)

// CURRENT MEASUREMENT
#define HALL_ADC_PIN A10  // Hall effect current sensor (12-bit ADC)

// VOLTAGE MEASUREMENT (MAX22530 SPI ADC)
// UNUSED
#define MAX22530_CS_PIN 0 // Chip select for MAX22530

// SPEED MEASUREMENT (ENCODER)
#define ENC_A_PIN 2       // Encoder channel A (primary quadrature)
#define ENC_B_PIN 3       // Encoder channel B (secondary quadrature)

#endif // PINS_H

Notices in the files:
README.md:
License: CC BY-NC-SA 4.0
